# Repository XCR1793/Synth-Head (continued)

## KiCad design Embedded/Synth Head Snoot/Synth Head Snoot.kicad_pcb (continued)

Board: 2 copper layers, 27 parts (0 on the bottom side), 16 nets, no tracks yet.

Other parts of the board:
C5, C6: 1uF; R_0603_1608Metric
C7: 10uF; C_0603_1608Metric
U3: AP7366-33W5-7; AP7366

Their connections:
+3V3: C6.1, C7.1, U3.5 (Vout); also elsewhere on the board
/3V3 Regulator/Vin: C5.1, U3.1 (VCC), U3.3 (EN); also elsewhere on the board
GND: C5.2, C6.2, C7.2, U3.2 (GND); also elsewhere on the board

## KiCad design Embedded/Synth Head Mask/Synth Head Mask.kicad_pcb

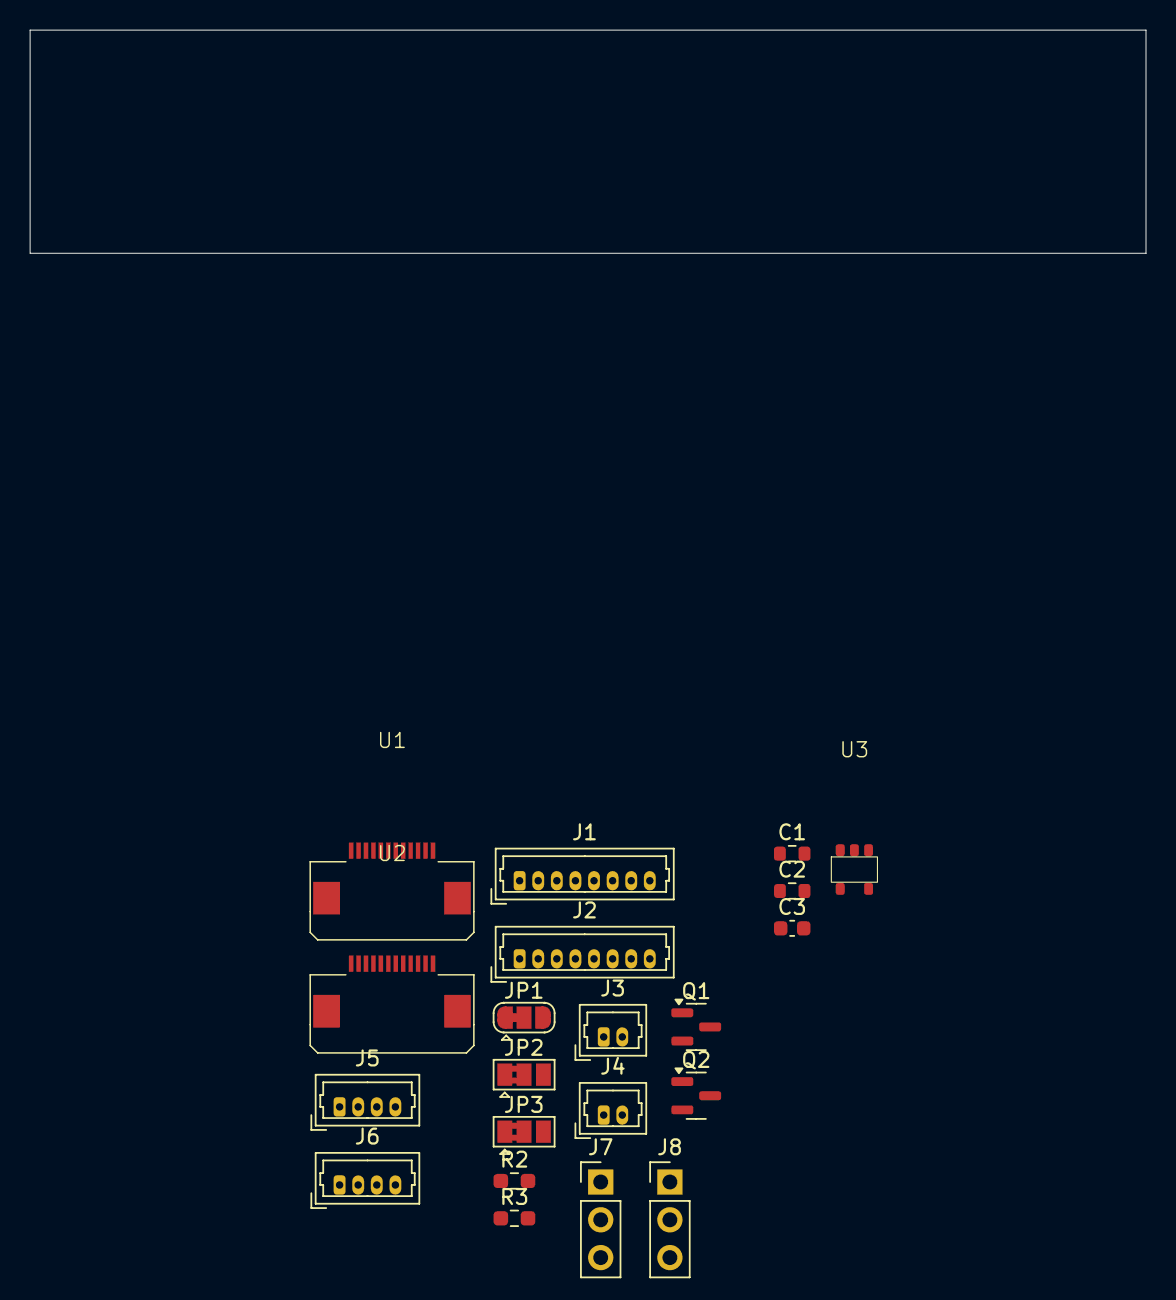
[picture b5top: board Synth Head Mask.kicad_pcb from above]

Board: 2 copper layers, 75.0 x 15.0 mm, 21 parts (0 on the bottom side), 18 nets, no tracks yet.

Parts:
C1, C2: 1uF; R_0603_1608Metric
C3: 10uF; C_0603_1608Metric
J1: JST [S]; Molex_PicoBlade_53047-0810_1x08_P1.25mm_Vertical
J2: JST [M]; Molex_PicoBlade_53047-0810_1x08_P1.25mm_Vertical
J3, J4: JST [F]; Molex_PicoBlade_53047-0210_1x02_P1.25mm_Vertical
J5: JST [B]; Molex_PicoBlade_53047-0410_1x04_P1.25mm_Vertical
J6: JST [K]; Molex_PicoBlade_53047-0410_1x04_P1.25mm_Vertical
J7, J8: Misc Expansion; PinHeader_1x03_P2.54mm_Vertical
JP1: LR Select; SolderJumper-3_P1.3mm_Bridged12_RoundedPad1.0x1.5mm
JP2, JP3: Expansion PWR; SolderJumper-3_P1.3mm_Bridged2Bar12_Pad1.0x1.5mm
Q1: BSS138; SOT-23
Q2: AS2302; SOT-23
R2, R3: 10K; R_0603_1608Metric_Pad0.98x0.95mm_HandSolder
U1: FFC [M]; FFC Aliexpress 0.5mm 12P
U2: FFC [S]; FFC Aliexpress 0.5mm 12P
U3: AP7366-33W5-7; AP7366

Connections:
+3V3: C2.1, C3.1, J1.3, J1.6, J2.3, J2.6, JP1.3 (B), JP2.1 (A), JP3.1 (A), Q1.1 (G), R2.1, U3.5 (Vout)
+5V: C1.1, J5.2, J5.3, J6.2, J6.3, JP2.3 (B), JP3.3 (B), Q2.3 (D), R3.1, U1.5, U1.8, U2.5, U2.8, U3.1 (VCC), U3.3 (EN)
CPU IO 0: J7.2, U1.4
CPU IO 1: J8.2, U1.9
Fan PWR: J3.1, J4.1, Q2.2 (S)
GND: C1.2, C2.2, C3.2, J1.1, J1.2, J1.7, J1.8, J2.1, J2.8, J3.2, J4.2, J5.1, J5.4, J6.1, J6.4, J7.3, J8.3, JP1.1 (A), U1.1, U1.2, U1.3, U1.10, U1.11, U1.12, U2.1, U2.12, U3.2 (GND)
unnamed: J2.7, JP1.2 (C)
unnamed: J7.1, JP2.2 (C)
unnamed: J8.1, JP3.2 (C)
unnamed: Q1.3 (D), Q2.1 (G), R3.2
Snoot IO 0: Q1.2 (S), R2.2, U2.4
Snoot RX: U1.6, U2.6
Snoot SCK: J2.4, U2.11
Snoot SCL: J1.4, U2.3
Snoot SD: J2.2, U2.9
Snoot SDA: J1.5, U2.2
Snoot TX: U1.7, U2.7
Snoot WS: J2.5, U2.10

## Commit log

2024-08-27 General Update
2024-12-02 Begun Diagrams & Electronics
2024-12-04 Finished electrical overview schematic
2024-12-05 Updated which electronic components were placed in the CAD
2024-12-05 Preparing Datasheets & KiCAD Projects
2024-12-06 Substructure Ports Defined
2024-12-06 Mask Board & Snoot Ports Defined
2024-12-06 PDU Ports Define (Main Management)
2024-12-06 Added Dedicated Power Connections Map
2024-12-06 KiCAD Summaries, Connections & Feature Descriptions
2024-12-06 Added PCBs & Schematics to DX.3 (Rushed)
2024-12-06 Added some component selection in KiCAD
2024-12-07 KiCAD Added the schematics to drive some sensors
2024-12-07 Some Sensors Added to the GPU and CPU
2024-12-07 Majority of the pins for the Mask Board & Snoot Added
2024-12-08 Added Cable Lengths to the Connections Diagram
2024-12-08 Cable Management for the Circuit Boards
2024-12-08 Added Power and USBC to GPU
2024-12-08 GPU Port Assignments & Sensors Confirmed
2024-12-08 CPU Power & USB C Port Added
2024-12-08 CPU FFC Ports Added
2024-12-09 Added GPS & Micro SD Card
2024-12-09 Added I2C GPIO Expansion to GPU & Some Pin Position Updates
2024-12-09 Added Voltage Buffer & Modified Sheet Hierarchy
2024-12-09 Added Speaker, Power & USB C to Snoot Board
2024-12-09 Updated Some Diagram Aesthetics
2024-12-09 Nearly completed Mask Board
2024-12-09 Added Touch Pad to Snoot
2024-12-10 Added GPS RF Port
2024-12-10 Added Indicator Power LEDS & some Decoupling Caps
2024-12-10 Added Power Indicator LEDS & Decoupling Caps
2024-12-10 PDU Schematic Basically Completed
2024-12-10 PDU Nearly Complete
2024-12-11 Added Jaw LEDS
2024-12-11 Prepared All Main Boards for PCB Creation
2024-12-11 Added Misc Boards & Adapters
2024-12-12 Prepared Circuits for Routing and Placement Tuning
2024-12-12 CPU PCB Done
2024-12-13 GPU Routed All but pins to ESP32
2024-12-14 Test Update
